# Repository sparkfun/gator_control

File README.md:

SparkFun gator:control ProtoSnap
========================================

[*SparkFun gator:control - COM-14968*](https://www.sparkfun.com/products/14968)

The gator:control breaks out several buttons and switches into an alligator clippable format for use with micro:bit as well as the gator:bit expansion for micro:bit.

Repository Contents
-------------------
* **/Firmware** - Example code used in the gator:control. While they are compiled HEX codes, you can modify the example code once they are imported into MakeCode editor.
* **/Hardware** - Eagle design files (.brd, .sch)
* **/Production** - Production panel files (.brd)

Documentation
--------------
* **[Hookup Guide](https://learn.sparkfun.com/tutorials/gatorcontrol-protosnap-hookup-guide)** - Basic hookup guide for the gator:control.

Product Versions
----------------
* [COM-14968](https://www.sparkfun.com/products/14968)- The gator:control is a few gator-clippable buttons and switches.

License Information
-------------------

This product is _**open source**_! 

Please review the LICENSE.md file for license information. 

If you have any questions or concerns on licensing, please contact techsupport@sparkfun.com.

Distributed as-is; no warranty is given.

- Your friends at SparkFun.

_<COLLABORATION CREDIT>_

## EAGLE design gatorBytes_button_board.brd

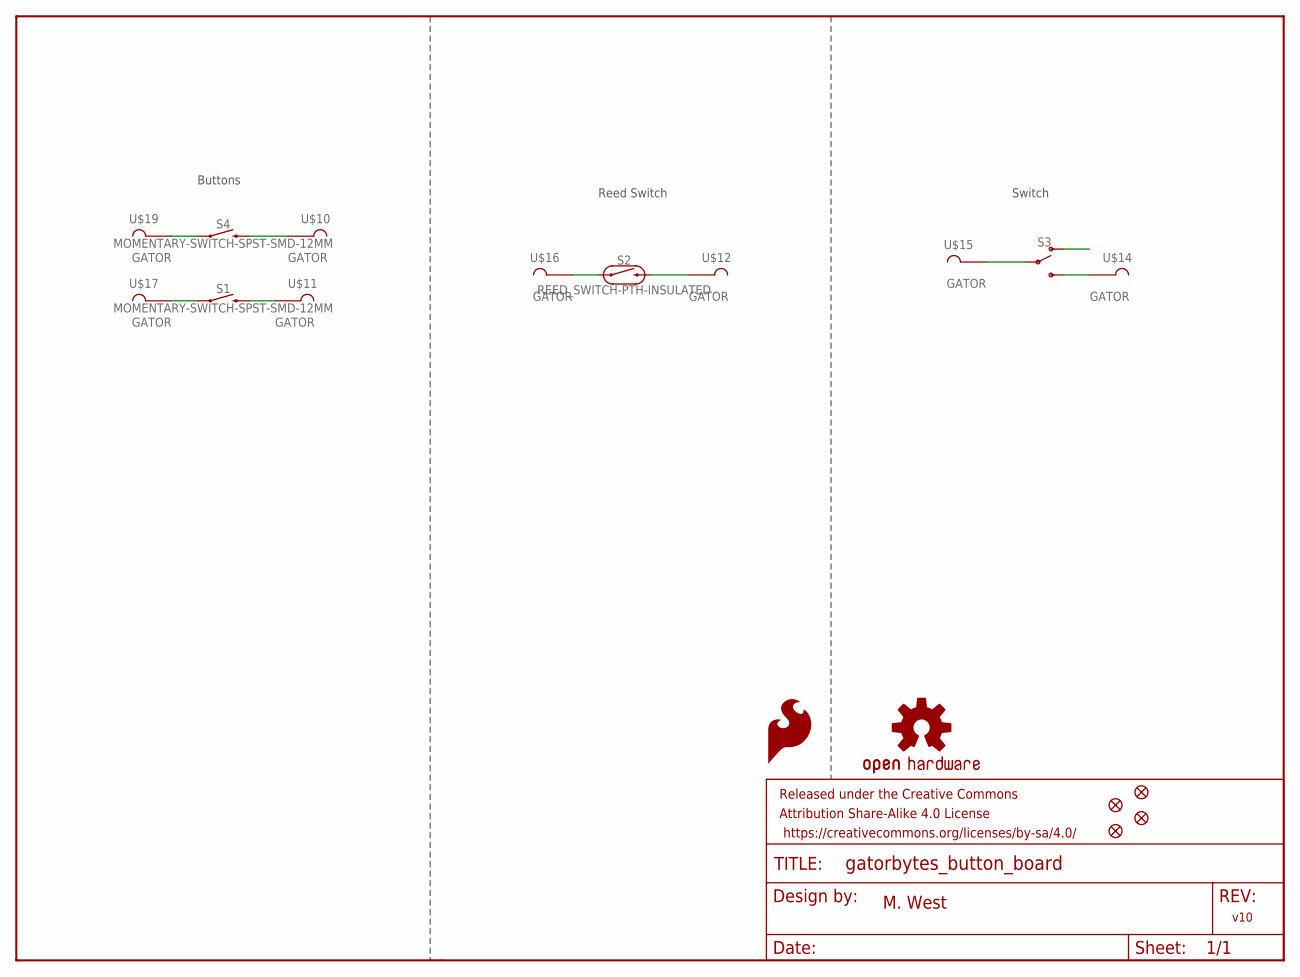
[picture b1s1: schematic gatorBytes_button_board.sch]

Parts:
FD1, FD2, FD3, FD4: FIDUCIALUFIDUCIAL; FIDUCIAL-MICRO
FRAME1: FRAME-LETTER; CREATIVE_COMMONS
LOGO1: SFE_LOGO_FLAME.1_INCH; SFE_LOGO_FLAME_.1
LOGO2: OSHW-LOGOS; OSHW-LOGO-S
S1, S4: MOMENTARY-SWITCH-SPST-SMD-12MM; TACTILE_SWITCH_SMD_12MM
S2: REED_SWITCH-PTH-INSULATED; REED_SWITCH_PLASTIC
S3: SWITCH-SPDT-SMD-AYZ0202; SWITCH_DPDT_SMD_AYZ0202
U$10, U$11, U$12, U$14, U$15, U$16, U$17, U$19: GATOR

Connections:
unnamed: S4.1, U$19.P$1, U$19.P$2
unnamed: S4.3 (2), U$10.P$1, U$10.P$2
unnamed: S1.1, U$17.P$1, U$17.P$2
unnamed: S1.3 (2), U$11.P$1, U$11.P$2
unnamed: S2.P$1 (1), U$16.P$1, U$16.P$2
unnamed: S2.P$2 (2), U$12.P$1, U$12.P$2
unnamed: S3.2, U$15.P$1, U$15.P$2
unnamed: S3.3 (S), U$14.P$1, U$14.P$2

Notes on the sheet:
M. West
v10
Buttons
Reed Switch
Switch

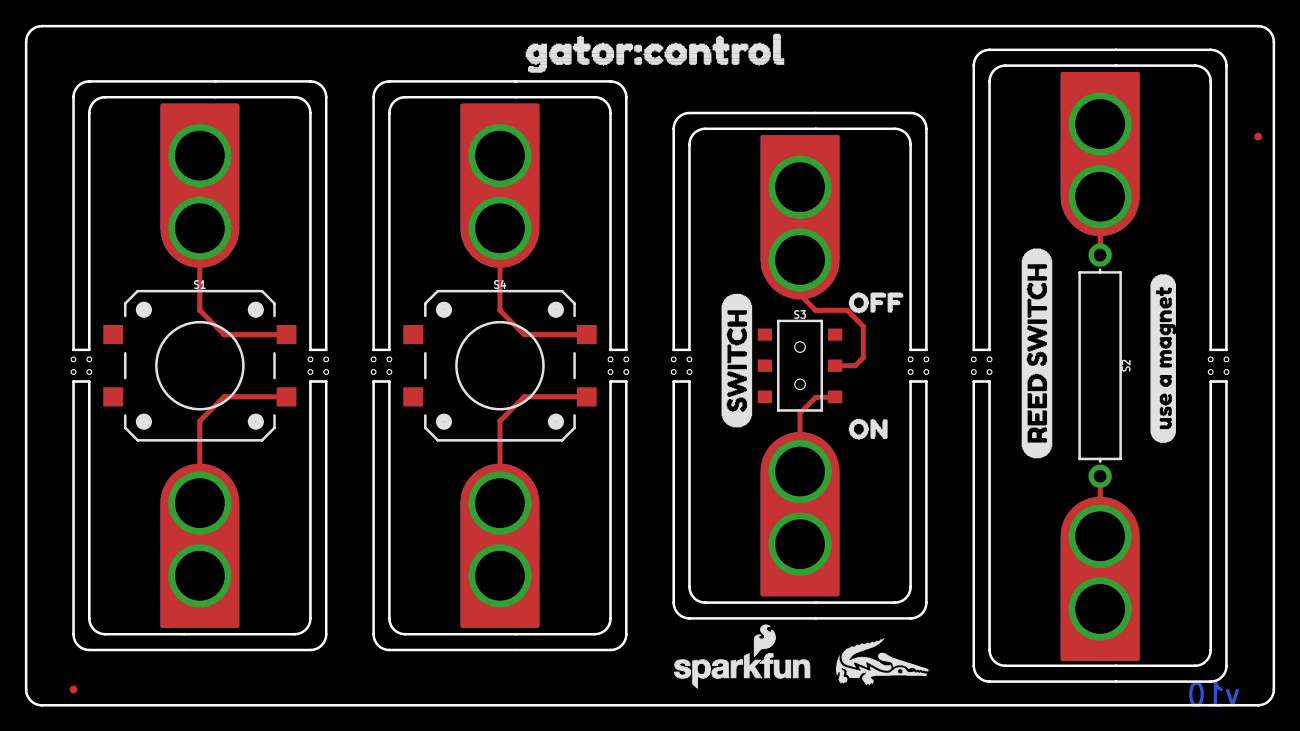
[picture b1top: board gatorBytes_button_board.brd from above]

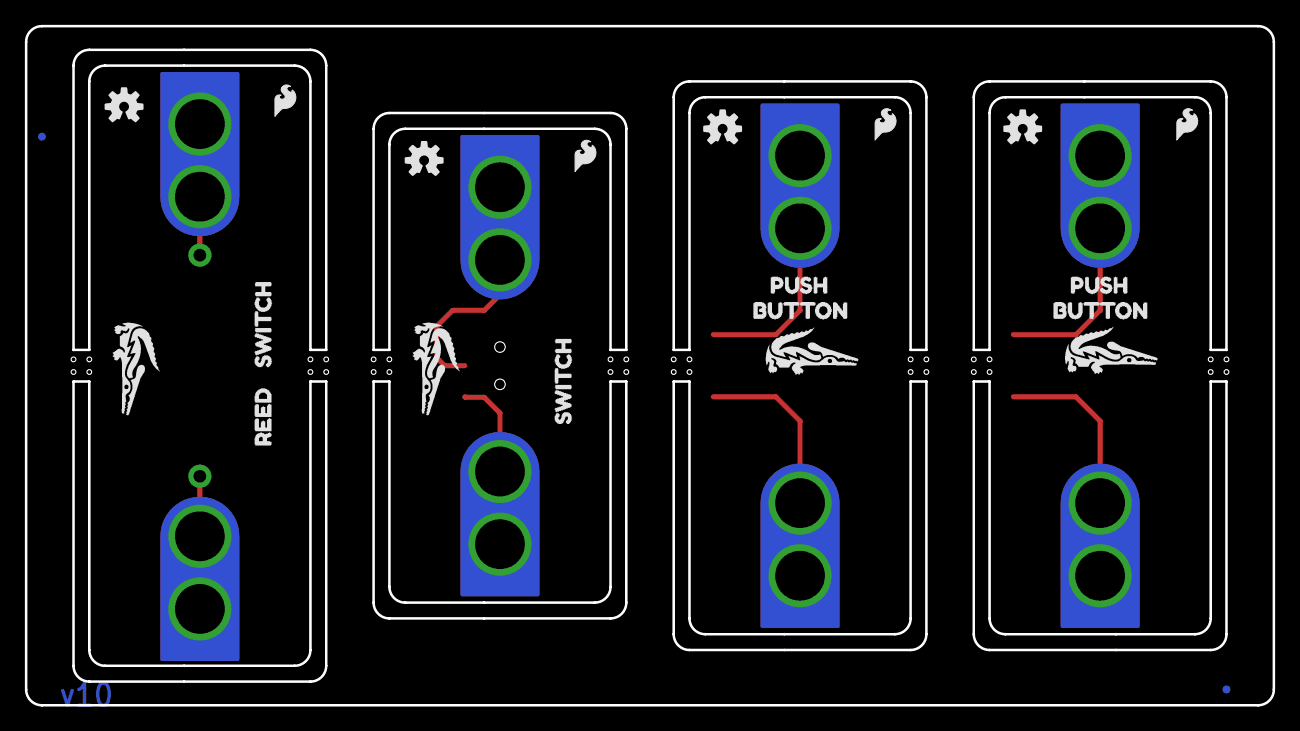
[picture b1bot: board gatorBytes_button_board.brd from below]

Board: 2 copper layers, 100.3 x 54.6 mm, 45 parts (21 on the bottom side), 8 nets.

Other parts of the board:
LOGO3, LOGO5, LOGO8: OSHW-LOGOS; OSHW-LOGO-S
LOGO4, LOGO6, LOGO7: SFE_LOGO_FLAME.1_INCH; SFE_LOGO_FLAME_.1
U$1, U$22, U$28, U$29, U$70: GATOR#PNG
U$2, U$5: BUTTON3
U$3, U$4: PUSH4
U$6: OFF9
U$7: REED_SWITCH0
U$8: SWITCH2
U$9: USE_A_MAGNET10
U$13: ON8
U$18, U$21: SWITCH5
U$20: REED6
U$23: GATOR#CONTROL0
U$24: SFE_LOGO_NAME_FLAME_.1
U$33: ORDERING_INSTRUCTIONS

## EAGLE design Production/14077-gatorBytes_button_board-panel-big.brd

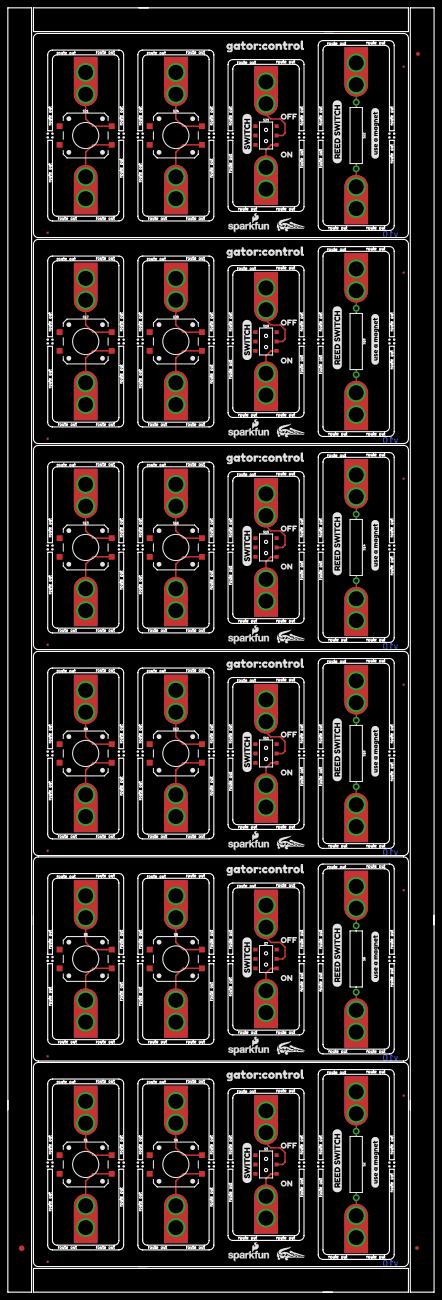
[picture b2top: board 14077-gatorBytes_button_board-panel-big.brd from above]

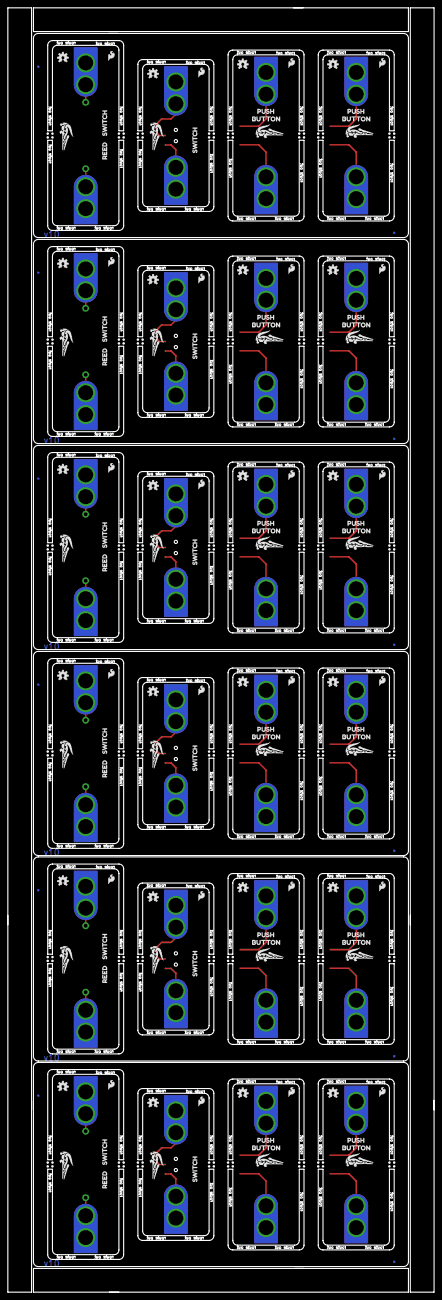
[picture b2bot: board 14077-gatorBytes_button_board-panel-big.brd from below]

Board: 2 copper layers, 114.0 x 343.7 mm, 261 parts (126 on the bottom side), 48 nets.

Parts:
E$1, E$7: FIDUCIAL-1X2
E$6: FIDUCIAL-1.5X3
FD1, FD2, FD3, FD4, FD5, FD6, FD7, FD8, FD9, FD10, FD11, FD12, FD13, FD14, FD15, FD16, FD17, FD18, FD19, FD20, FD21, FD22, FD23, FD24: FIDUCIALUFIDUCIAL; FIDUCIAL-MICRO
LOGO1, LOGO4, LOGO6, LOGO7, LOGO9, LOGO12, LOGO14, LOGO15, LOGO17, LOGO20, LOGO22, LOGO23, LOGO25, LOGO28, LOGO30, LOGO31, LOGO33, LOGO36, LOGO38, LOGO39, LOGO41, LOGO44, LOGO46, LOGO47: SFE_LOGO_FLAME.1_INCH; SFE_LOGO_FLAME_.1
LOGO2, LOGO3, LOGO5, LOGO8, LOGO10, LOGO11, LOGO13, LOGO16, LOGO18, LOGO19, LOGO21, LOGO24, LOGO26, LOGO27, LOGO29, LOGO32, LOGO34, LOGO35, LOGO37, LOGO40, LOGO42, LOGO43, LOGO45, LOGO48: OSHW-LOGOS; OSHW-LOGO-S
S1, S4, S5, S8, S9, S12, S13, S16, S17, S20, S21, S24: MOMENTARY-SWITCH-SPST-SMD-12MM; TACTILE_SWITCH_SMD_12MM
S2, S6, S10, S14, S18, S22: REED_SWITCH-PTH-INSULATED; REED_SWITCH_PLASTIC
S3, S7, S11, S15, S19, S23: SWITCH_DPDT_SMD_AYZ0202
U$1, U$22, U$25, U$26, U$27, U$28, U$29, U$38, U$51, U$54, U$55, U$56, U$65, U$70, U$79, U$82, U$83, U$84, U$93, U$106, U$109, U$110, U$111, U$120, U$133, U$136, U$137, U$138, U$147, U$160: GATOR#PNG
U$2, U$5, U$39, U$42, U$66, U$69, U$94, U$97, U$121, U$124, U$148, U$151: BUTTON3
U$3, U$4, U$40, U$41, U$67, U$68, U$95, U$96, U$122, U$123, U$149, U$150: PUSH4
U$6, U$46, U$74, U$101, U$128, U$155: OFF9
U$7, U$43, U$71, U$98, U$125, U$152: REED_SWITCH0
U$8, U$44, U$72, U$99, U$126, U$153: SWITCH2
U$9, U$45, U$73, U$100, U$127, U$154: USE_A_MAGNET10
U$10, U$11, U$12, U$14, U$15, U$16, U$17, U$19, U$30, U$31, U$32, U$33, U$34, U$35, U$36, U$37, U$57, U$58, U$59, U$60, U$61, U$62, U$63, U$64, U$85, U$86, U$87, U$88, U$89, U$90, U$91, U$92, U$112, U$113, U$114, U$115, U$116, U$117, U$118, U$119, U$139, U$140, U$141, U$142, U$143, U$144, U$145, U$146: GATOR
U$13, U$47, U$75, U$102, U$129, U$156: ON8
U$18, U$21, U$48, U$50, U$76, U$78, U$103, U$105, U$130, U$132, U$157, U$159: SWITCH5
U$20, U$49, U$77, U$104, U$131, U$158: REED6
U$23, U$52, U$80, U$107, U$134, U$161: GATOR#CONTROL0
U$24, U$53, U$81, U$108, U$135, U$162: SFE_LOGO_NAME_FLAME_.1

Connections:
unnamed: S4.1, U$19.P$1, U$19.P$2
unnamed: S4.3, U$10.P$1, U$10.P$2
unnamed: S1.1, U$17.P$1, U$17.P$2
unnamed: S1.3, U$11.P$1, U$11.P$2
unnamed: S2.P$1, U$16.P$1, U$16.P$2
unnamed: S2.P$2, U$12.P$1, U$12.P$2
unnamed: S3.2, U$15.P$1, U$15.P$2
unnamed: S3.3, U$14.P$1, U$14.P$2
unnamed: S8.1, U$37.P$1, U$37.P$2
unnamed: S8.3, U$30.P$1, U$30.P$2
unnamed: S5.1, U$36.P$1, U$36.P$2
unnamed: S5.3, U$31.P$1, U$31.P$2
unnamed: S6.P$1, U$35.P$1, U$35.P$2
unnamed: S6.P$2, U$32.P$1, U$32.P$2
unnamed: S7.2, U$34.P$1, U$34.P$2
unnamed: S7.3, U$33.P$1, U$33.P$2
unnamed: S12.1, U$64.P$1, U$64.P$2
unnamed: S12.3, U$57.P$1, U$57.P$2
unnamed: S9.1, U$63.P$1, U$63.P$2
unnamed: S9.3, U$58.P$1, U$58.P$2
unnamed: S10.P$1, U$62.P$1, U$62.P$2
unnamed: S10.P$2, U$59.P$1, U$59.P$2
unnamed: S11.2, U$61.P$1, U$61.P$2
unnamed: S11.3, U$60.P$1, U$60.P$2
unnamed: S16.1, U$92.P$1, U$92.P$2
unnamed: S16.3, U$85.P$1, U$85.P$2
unnamed: S13.1, U$91.P$1, U$91.P$2
unnamed: S13.3, U$86.P$1, U$86.P$2
unnamed: S14.P$1, U$90.P$1, U$90.P$2
unnamed: S14.P$2, U$87.P$1, U$87.P$2
unnamed: S15.2, U$89.P$1, U$89.P$2
unnamed: S15.3, U$88.P$1, U$88.P$2
unnamed: S20.1, U$119.P$1, U$119.P$2
unnamed: S20.3, U$112.P$1, U$112.P$2
unnamed: S17.1, U$118.P$1, U$118.P$2
unnamed: S17.3, U$113.P$1, U$113.P$2
unnamed: S18.P$1, U$117.P$1, U$117.P$2
unnamed: S18.P$2, U$114.P$1, U$114.P$2
unnamed: S19.2, U$116.P$1, U$116.P$2
unnamed: S19.3, U$115.P$1, U$115.P$2
unnamed: S24.1, U$146.P$1, U$146.P$2
unnamed: S24.3, U$139.P$1, U$139.P$2
unnamed: S21.1, U$145.P$1, U$145.P$2
unnamed: S21.3, U$140.P$1, U$140.P$2
unnamed: S22.P$1, U$144.P$1, U$144.P$2
unnamed: S22.P$2, U$141.P$1, U$141.P$2
unnamed: S23.2, U$143.P$1, U$143.P$2
unnamed: S23.3, U$142.P$1, U$142.P$2

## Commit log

2018-08-23 removing pth
2018-09-12 pre design review
2018-09-12 post design review
2018-09-13 post checklist changes
2018-09-13 post qc review
2018-09-14 created panel v10
2018-10-18 cleaning repo, readme
2018-10-18 updating readme
2018-10-18 fixing readme
2018-11-19 panel
2019-01-09 gator:control Example Code HEX files
    Add compiled MakeCode example code used with the gator:control board

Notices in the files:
parts and their libraries:
SparkFun-Aesthetics: Licensing: Creative Commons ShareAlike 4.0 International - https://creativecommons.org/licenses/by-sa/4.0
SparkFun-Aesthetics: Released under the Creative Commons Attribution Share-Alike 4.0 License
SparkFun-Aesthetics: https://creativecommons.org/licenses/by-sa/4.0
